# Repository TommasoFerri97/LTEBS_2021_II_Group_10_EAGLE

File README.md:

# Electronic technologies and biosensors laboratory
> 2021 - II semester - First Assignment

## Authors (Group 10)
  - [**Dario Comini**](https://github.com/DarioComini) 
  - [**Tommaso Ferri**](https://github.com/TommasoFerri97)

## Description
Design a schematic, a PCB, and custom devices using Autodesk EAGLE software.

### Context
Your company, the LTEBS srl, would like to use the PSoC 5LP micro-controller in a project requested by a customer. In order to evaluate the performance of the micro-controller and to determine if such uC is suitable for the project, the R&D department would like to design a PCB embedding the PSoC 5LP. This way, testing and assessment of the performance would be a lot easier than using a simple breadboard. As Cypress offers a development kit for the PSoC 5LP, namely the CY8CKIT-059, you are requested to design a PCB embedding suck kit, which will be soldered on male jumpers, and additional components required to conduct the proper testing by the R&D department. As some of the requested components are not present in EAGLE installation libraries, you are required to design a library containing such components. The PCB will be manufactured by [MDSrl](https://www.mdsrl.it/).

Starting from a schematic and a list of components, create the associated PCB. Route all the components, and check that the ratsnest command does not provide any error message. Create a design rule files according to the technical specifications reported in the manufacturer website. Perform a DRC (Design Rule Check) using the created DRC file and check that no error or warning is generated.

### Repository structure
- **Library**: Contains EAGLE library files
  - *"Group_10_Library.lbr"*: library file for devices [TMUX1208](https://www.ti.com/lit/ds/symlink/tmux1208.pdf) and [TCA9546A](https://www.ti.com/lit/ds/symlink/tca9546a.pdf)
- **Project**: Contains EAGLE schematic and board files
  - *"Group_10.sch"*: schematic file
  - *"Group_10.brd"*: board file
- **Design Rules**: Contains EAGLE design rules file
  - *"Group_10.dru"*: design rules file, following [manufacturer's specifications](https://www.mdsrl.it/mddesignrules.html)

### Additional resources
The following documents/tutorial can be useful for this assignment:
- [SparkFun EAGLE Tutorial](https://learn.sparkfun.com/tutorials/using-eagle-schematic/all)
- [EAGLE Layers](https://www.autodesk.com/products/eagle/blog/every-layer-explained-autodesk-eagle/)
- [Getting Started with EAGLE](https://www.autodesk.com/products/eagle/overview)

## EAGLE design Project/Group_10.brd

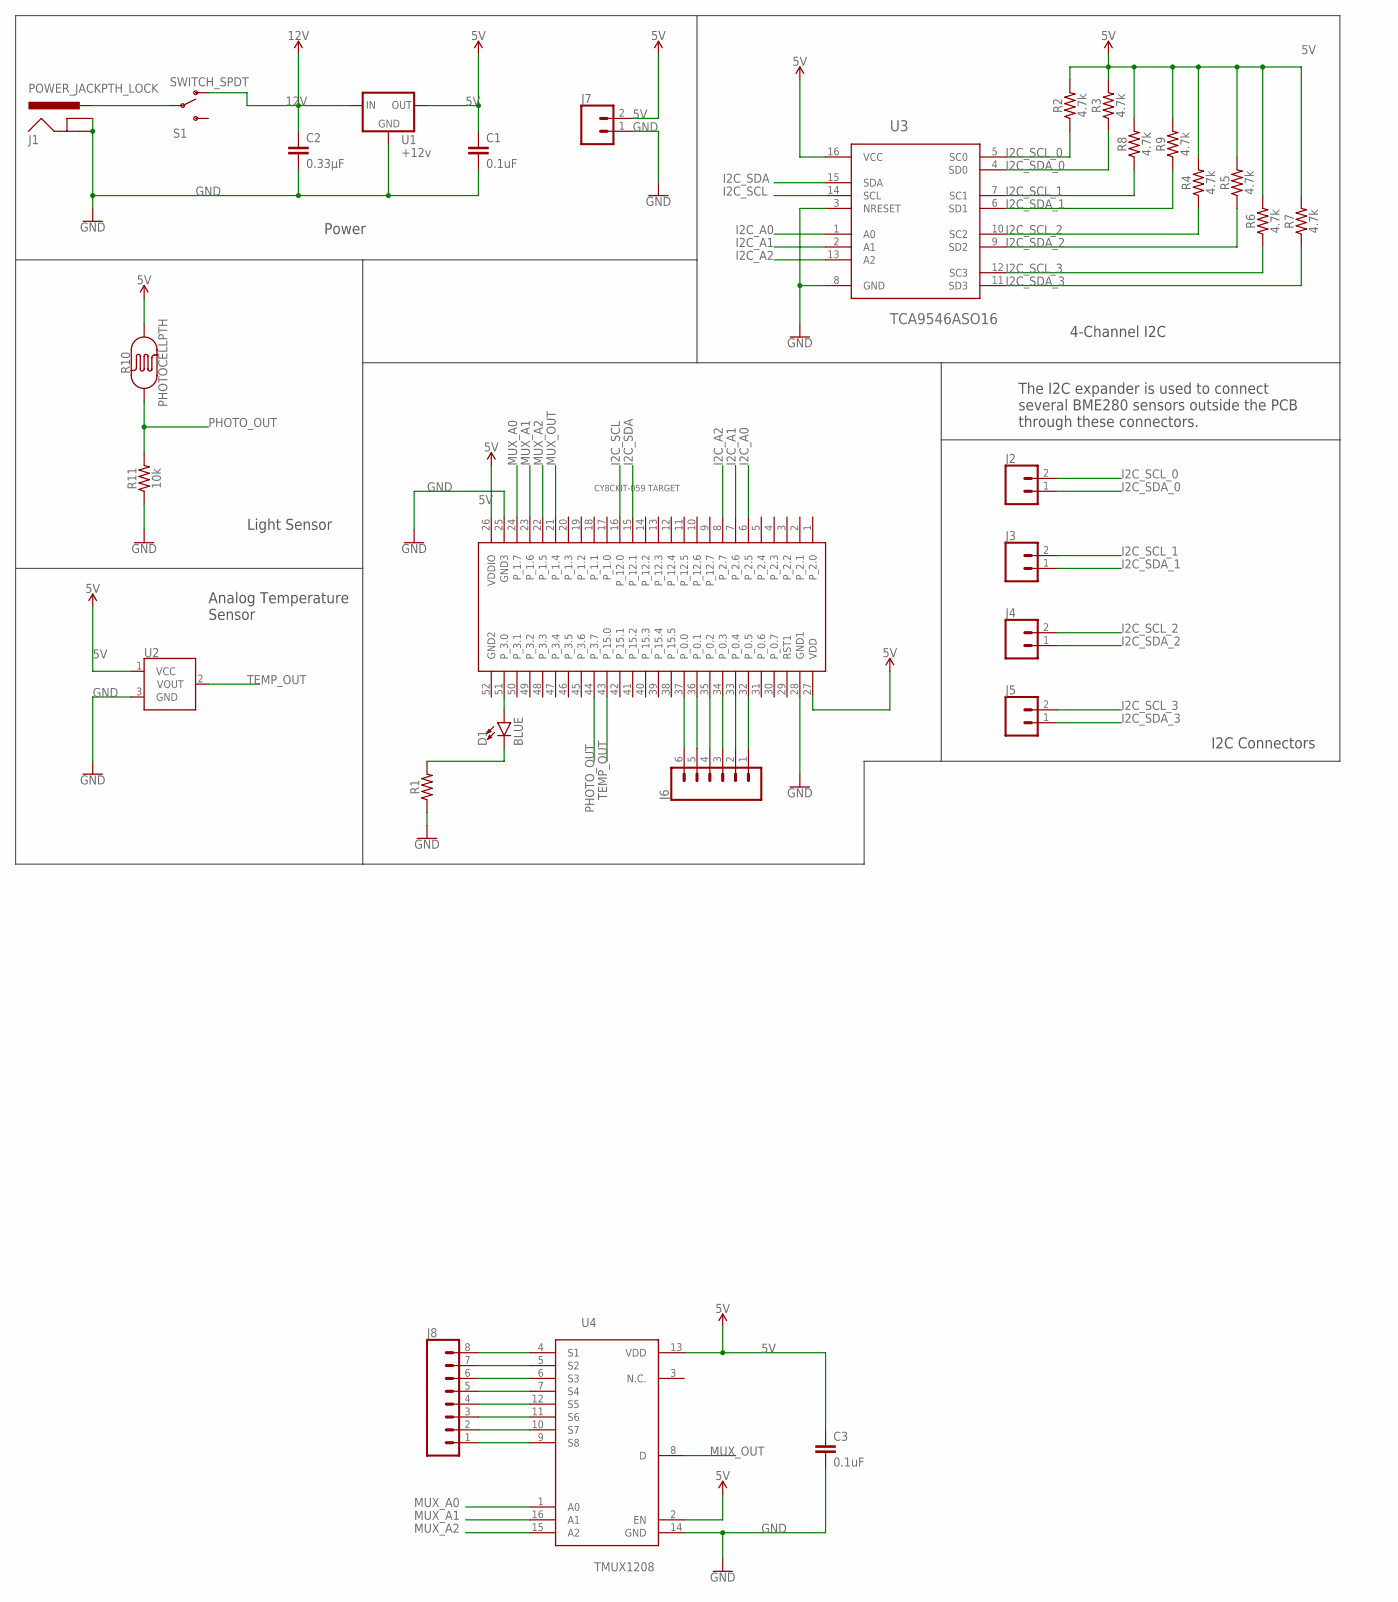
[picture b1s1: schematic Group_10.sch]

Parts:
C1, C3: 0.1uF; CAP-PTH-SMALL-KIT
C2: 0.33µF; 0805
D1: BLUE; LED-1206
J1: POWER_JACKPTH_LOCK; POWER_JACK_PTH_LOCK
J2, J3, J4, J5, J7: CONN_02; 1X02
J6: CONN_06LOCK; 1X06_LOCK
J8: CONN_08"; 1X08
R1: AXIAL-0.3
R2, R3, R4, R5, R6, R7, R8, R9: 4.7k; 0603
R10: PHOTOCELLPTH; PHOTOCELL
R11: 10k; 0603
S1: SWITCH_SPDT; KPS-1290
U1: +12v; TO-252
U2: TMP36GT9; TO-92
U3: TCA9546ASO16; TSSOP16
U4: TMUX1208; QFN16
U$2: CY8CKIT-059_TARGET_3

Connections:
5V: C1.1, C3.1, J7.2, R2.2, R3.2, R4.2, R5.2, R6.2, R7.2, R8.2, R9.2, R10.2, U1.2 (OUT), U2.1 (VCC), U3.16 (VCC), U4.2 (EN), U4.13 (VDD), U$2.26 (VDDIO), U$2.27 (VDD)
12V: C2.1, S1.O, U1.1 (IN)
GND: C1.2, C2.2, C3.2, J1.GND, J1.GNDBREAK, J7.1, R1.P$1 (1), R11.1, U1.3 (GND), U2.3 (GND), U3.3 (NRESET), U3.8 (GND), U4.14 (GND), U$2.25 (GND3), U$2.28 (GND1)
GND2: U$2.52 (GND2)
I2C_A0: U3.1 (A0), U$2.6 (P_2.5)
I2C_A1: U3.2 (A1), U$2.7 (P_2.6)
I2C_A2: U3.13 (A2), U$2.8 (P_2.7)
I2C_SCL: U3.14 (SCL), U$2.16 (P_12.0)
I2C_SCL_0: J2.2, R2.1, U3.5 (SC0)
I2C_SCL_1: J3.2, R8.1, U3.7 (SC1)
I2C_SCL_2: J4.2, R4.1, U3.10 (SC2)
I2C_SCL_3: J5.2, R6.1, U3.12 (SC3)
I2C_SDA: U3.15 (SDA), U$2.15 (P_12.1)
I2C_SDA_0: J2.1, R3.1, U3.4 (SD0)
I2C_SDA_1: J3.1, R9.1, U3.6 (SD1)
I2C_SDA_2: J4.1, R5.1, U3.9 (SD2)
I2C_SDA_3: J5.1, R7.1, U3.11 (SD3)
MUX_A0: U4.1 (A0), U$2.24 (P_1.7)
MUX_A1: U4.16 (A1), U$2.23 (P_1.6)
MUX_A2: U4.15 (A2), U$2.22 (P_1.5)
MUX_OUT: U4.8 (D), U$2.21 (P_1.4)
unnamed: J1.PWR, S1.P
unnamed: D1.A, U$2.51 (P_3.0)
unnamed: D1.C, R1.P$2 (2)
unnamed: J6.1, U$2.32 (P_0.5)
unnamed: J6.2, U$2.33 (P_0.4)
unnamed: J6.3, U$2.34 (P_0.3)
unnamed: J6.4, U$2.35 (P_0.2)
unnamed: J6.5, U$2.36 (P_0.1)
unnamed: J6.6, U$2.37 (P_0.0)
unnamed: J8.8, U4.4 (S1)
unnamed: J8.7, U4.5 (S2)
unnamed: J8.6, U4.6 (S3)
unnamed: J8.5, U4.7 (S4)
unnamed: J8.4, U4.12 (S5)
unnamed: J8.3, U4.11 (S6)
unnamed: J8.2, U4.10 (S7)
unnamed: J8.1, U4.9 (S8)
PHOTO_OUT: R10.1, R11.2, U$2.44 (P_3.7)
TEMP_OUT: U2.2 (VOUT), U$2.43 (P_15.0)

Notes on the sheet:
4-Channel I2C
Power
Light Sensor
Analog Temperature Sensor
I2C Connectors
The I2C expander is used to connect several BME280 sensors outside the PCB through these connectors.

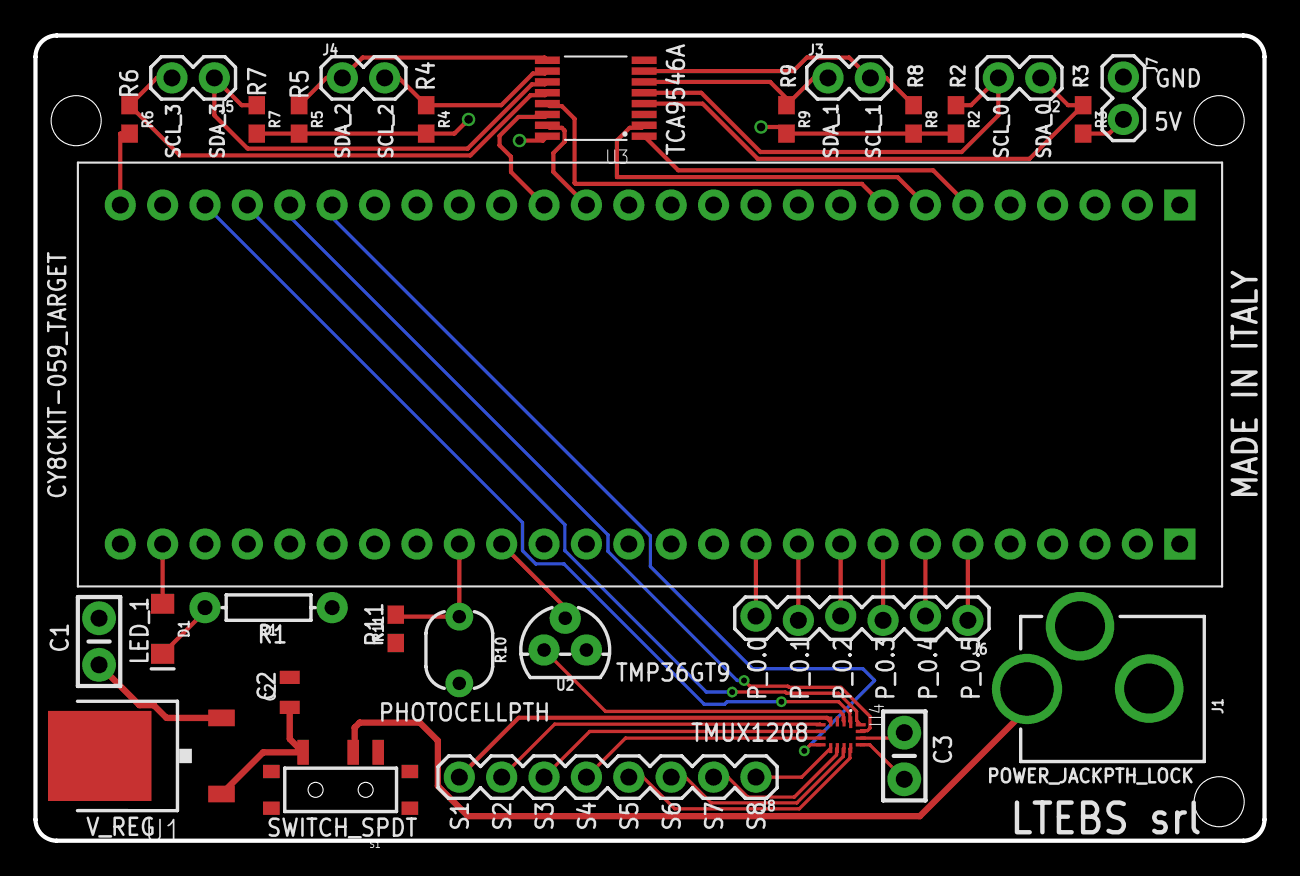
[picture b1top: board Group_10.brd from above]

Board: 2 copper layers, 73.7 x 48.3 mm, 29 parts (0 on the bottom side), 39 nets.

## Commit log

2021-03-18 first commit - added schematic file with some components
2021-03-18 added empty library
2021-03-18 created footprint QFN16
2021-03-18 TMUX1208 device added with description to the new created library
2021-03-18 removed library backup files from git tracking
2021-03-18 added exclusion rule for library backup files to gitignore
2021-03-19 full schematic without TCA9546A
2021-03-19 third gitignore update
2021-03-19 removed schematic backups from tracking and corrected gitignore to exclude further schematic backups
2021-03-19 TCA9546A device added with description to the library
2021-03-19 Added device TCA9546A to schematic and added value to R1
2021-03-20 added design rules file
2021-03-20 updated design rules with description
2021-03-20 added board file and connected all components
2021-03-20 added exclusion rule for board backup files in gitignore
2021-03-21 added silkscreen on top and bottom side to help in the main components placement
2021-03-22 corrected devices silkscreen distance from pads to match manifacturer's
2021-03-22 Updated devices on board, corrected isolate of copper pour, simplified some routing
2021-03-22 Corrected silkscreen font width to match manifacturer's, added some information and corrected some routing
2021-03-22 Corrected I2C_SDA_2 serigraphy
2021-03-22 Added M3 holes
2021-03-22 Increased width of power traces for possible current requirements
2021-03-22 added comments to the schematic
2021-03-23 Added smooth angles to the board
2021-03-23 Fixed device description and added link to datasheet
2021-03-23 Added README.md
2021-03-23 Corrected links in README.md
2021-03-23 Added silkscreen watermarks
2021-03-24 Update README.md
    README.md final version
2021-03-26 Corrected an error in schematic that caused some MUX connections to not be reflected in the board. Then connected them in the board
2021-03-26 Moved second frame to a second sheet
2021-03-26 Final version

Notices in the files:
parts and their libraries:
SparkFun-Capacitors: Licensing: Creative Commons ShareAlike 4.0 International - https://creativecommons.org/licenses/by-sa/4.0
